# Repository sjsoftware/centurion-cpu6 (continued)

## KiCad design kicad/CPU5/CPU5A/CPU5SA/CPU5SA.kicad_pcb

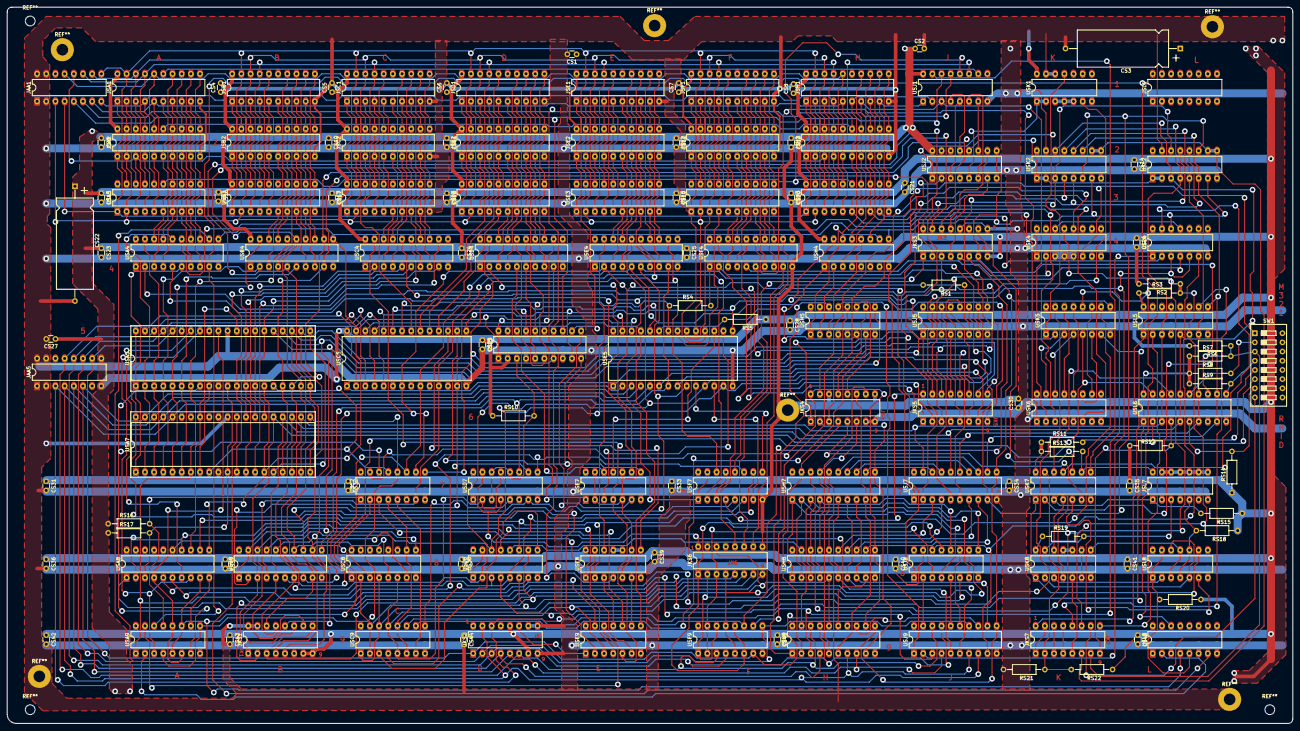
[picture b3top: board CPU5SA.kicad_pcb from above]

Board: 2 copper layers, 355.6 x 198.1 mm, 149 parts (0 on the bottom side), 305 nets.

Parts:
CS1, CS2, CS4, CS5, CS6, CS7, CS8, CS9, CS10, CS11, CS12, CS13, CS14, CS15, CS16, CS17, CS18, CS19, CS20, CS21, CS23, CS24, CS25, CS26, CS27, CS28, CS29, CS30, CS31, CS32, CS33, CS34, CS35, CS36, CS37, CS38, CS39, CS40, CS41, CS42, CS43, CS44, CS45, CS46: 100nF; C_Disc_D3.0mm_W1.6mm_P2.54mm
CS3, CS22: 150uF; CP_Axial_L25.0mm_D10.0mm_P31.75mm_Horizontal
JAA1, JAA5: Conn_02x08_Counter_Clockwise; DIP-16_W7.62mm_cent_socket
JKS1, JKS2, JKS3, JKS4, JKS5, JKS6, JKS7: Conn_02x08_Counter_Clockwise; DIP-16_W7.62mm_cent_socket_ud
JSA1: Conn_02x10_Counter_Clockwise; DIP-20_W7.62mm_cent_socket
JSA2: Conn_02x10_Counter_Clockwise; DIP-20_W7.62mm_cent_padsonly
JSB1: Conn_02x10_Counter_Clockwise; DIP-20_W7.62mm_cent_socket
JSB2: Conn_02x10_Counter_Clockwise; DIP-20_W7.62mm_cent_padsonly
JSC1: Conn_02x10_Counter_Clockwise; DIP-20_W7.62mm_cent_socket
JSC2: Conn_02x10_Counter_Clockwise; DIP-20_W7.62mm_cent_padsonly
JSD1: Conn_02x10_Counter_Clockwise; DIP-20_W7.62mm_cent_socket
JSD2: Conn_02x10_Counter_Clockwise; DIP-20_W7.62mm_cent_padsonly
JSE1: Conn_02x10_Counter_Clockwise; DIP-20_W7.62mm_cent_socket
JSE2: Conn_02x10_Counter_Clockwise; DIP-20_W7.62mm_cent_padsonly
JSF1: Conn_02x10_Counter_Clockwise; DIP-20_W7.62mm_cent_socket
JSF2: Conn_02x10_Counter_Clockwise; DIP-20_W7.62mm_cent_padsonly
JSH1: Conn_02x10_Counter_Clockwise; DIP-20_W7.62mm_cent_socket
JSH2: Conn_02x10_Counter_Clockwise; DIP-20_W7.62mm_cent_padsonly
JSL1: Conn_02x08_Counter_Clockwise; DIP-16_W7.62mm_cent_padsonly
JSL7: Conn_02x07_Counter_Clockwise; DIP-14_W7.62mm_cent_socket
RS1: 47R; R_Axial_DIN0207_L6.3mm_D2.5mm_P11.43mm_Horizontal
RS2, RS21: 330R; R_Axial_DIN0207_L6.3mm_D2.5mm_P11.43mm_Horizontal
RS3, RS7, RS22: 220R; R_Axial_DIN0207_L6.3mm_D2.5mm_P11.43mm_Horizontal
RS4: 100R; R_Axial_DIN0207_L6.3mm_D2.5mm_P11.43mm_Horizontal
RS5, RS10, RS13, RS15, RS16, RS18, RS19, RS20: 1k; R_Axial_DIN0207_L6.3mm_D2.5mm_P11.43mm_Horizontal
RS6: 330; R_Axial_DIN0207_L6.3mm_D2.5mm_P11.43mm_Horizontal
RS8, RS9, RS11, RS12, RS14: 4k7; R_Axial_DIN0207_L6.3mm_D2.5mm_P11.43mm_Horizontal
RS17: 470R; R_Axial_DIN0207_L6.3mm_D2.5mm_P11.43mm_Horizontal
SW1: SW_DIP_x08; SW_DIP_SPSTx08_Slide_9.78x22.5mm_W7.62mm_P2.54mm
USA3: 6349; DIP-20_W7.62mm_cent_socketchip
USA4, USA8: 74LS377; DIP-20_W7.62mm_cent
USA5, USA7: AM2901; DIP-40_W15.24mm_cent_socketchip
USA9: 74LS253; DIP-16_W7.62mm_cent
USB3: 6349; DIP-20_W7.62mm_cent_socketchip
USB4: 74LS377; DIP-20_W7.62mm_cent
USB8: 74LS240; DIP-20_W7.62mm_cent
USC3: 6349; DIP-20_W7.62mm_cent_socketchip
USC4: 74LS377; DIP-20_W7.62mm_cent
USC5: AM2909; DIP-28_W15.24mm_cent_socketchip
USC7: 74LS151; DIP-16_W7.62mm_cent
USC8: 74LS368; DIP-16_W7.62mm_cent
USC9: 74LS298; DIP-16_W7.62mm_cent
USD3: 6349; DIP-20_W7.62mm_cent_socketchip
USD4: 74LS377; DIP-20_W7.62mm_cent
USD5: AM2911; DIP-20_W7.62mm_cent_socketchip
USD7: 74LS151; DIP-16_W7.62mm_cent
USD8: 74LS153; DIP-16_W7.62mm_cent
USE3: 6349; DIP-20_W7.62mm_cent_socketchip
USE4: 74LS377; DIP-20_W7.62mm_cent
USE5: AM2909; DIP-28_W15.24mm_cent_socketchip
USE7, USE8: 74LS00; DIP-14_W7.62mm_cent
USE9: 74LS04; DIP-14_W7.62mm_cent
USF3: 6349; DIP-20_W7.62mm_cent_socketchip
USF4: 74LS377; DIP-20_W7.62mm_cent
USF7: 74LS153; DIP-16_W7.62mm_cent
USF9: 74LS298; DIP-16_W7.62mm_cent
USH3: 6349; DIP-20_W7.62mm_cent_socketchip
USH4: 74LS174; DIP-16_W7.62mm_cent
USH5: 74LS138; DIP-16_W7.62mm_cent
USH7, USH8: 74LS208; DIP-20_W7.62mm_cent_socket
USH9: 74LS377; DIP-20_W7.62mm_cent
USJ1: 74LS139; DIP-16_W7.62mm_cent
USJ2: 74LS174; DIP-16_W7.62mm_cent
USJ5: 74LS151; DIP-16_W7.62mm_cent
USJ7: 74LS374; DIP-20_W7.62mm_cent
USJ8: 74LS157; DIP-16_W7.62mm_cent
USJ9: 74LS377; DIP-20_W7.62mm_cent
USK1: 7437; DIP-14_W7.62mm_cent
USK2: 74LS173; DIP-16_W7.62mm_cent
USK4, USK6: 74LS138; DIP-16_W7.62mm_cent
USK5: 74LS174; DIP-16_W7.62mm_cent
USK7: 74LS04; DIP-14_W7.62mm_cent
USK8: 74LS00; DIP-14_W7.62mm_cent
USL2: 74LS173; DIP-16_W7.62mm_cent
USL4: 74LS02; DIP-14_W7.62mm_cent
USL5: 74LS368; DIP-16_W7.62mm_cent
USL6: 74LS240; DIP-20_W7.62mm_cent
USL8: 74LS74; DIP-14_W7.62mm_cent
USL9: 74LS153; DIP-16_W7.62mm_cent

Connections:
15MHz: JKS7.5, USK8.5
ALU.A0: USA5.4 (A0), USA7.4 (A0), USB4.2 (Q0)
ALU.A1: USA4.19 (Q7), USA5.3 (A1), USA7.3 (A1)
ALU.A2: USA4.16 (Q6), USA5.2 (A2), USA7.2 (A2)
ALU.A3: USA4.6 (Q2), USA5.1 (A3), USA7.1 (A3)
ALU.B0: JKS3.2, USA5.17 (B0), USA7.17 (B0), USB4.9 (Q3)
ALU.B1: JKS3.14, USA5.18 (B1), USA7.18 (B1), USB4.12 (Q4)
ALU.B2: JKS3.15, USA5.19 (B2), USA7.19 (B2), USB4.15 (Q5)
ALU.B3: JKS3.16, USA5.20 (B3), USA7.20 (B3), USB4.5 (Q1)
ALU.C: USA5.33 (Cn+4), USA8.8 (D3), USA9.3 (I3a)
ALU.HC: USA5.29 (Cn), USA7.33 (Cn+4), USA8.13 (D4)
ALU.I0: USA5.12 (I0), USA7.12 (I0), USC4.6 (Q2)
ALU.I1: USA5.13 (I1), USA7.13 (I1), USC4.9 (Q3)
ALU.I2: USA5.14 (I2), USA7.14 (I2), USC4.12 (Q4)
ALU.I3: USA5.26 (I3), USA7.26 (I3), USC4.15 (Q5)
ALU.I4: USA5.28 (I4), USA7.28 (I4), USC4.5 (Q1)
ALU.I5: USA5.27 (I5), USA7.27 (I5), USC4.2 (Q0)
ALU.I6: USA5.5 (I6), USA7.5 (I6), USB4.19 (Q7)
ALU.I7: USA5.7 (I7), USA7.7 (I7), USA9.1 (OEa), USB4.16 (Q6), USE9.13
ALU.I8: USA5.6 (I8), USA7.6 (I8), USB4.6 (Q2)
ALU.Q0: USA7.21 (Q0_LO/RI), USA9.4 (I2a), USA9.9 (Zb), USC7.12 (I7)
ALU.RAM0: USA5.16 (Q3_RO/LI), USA7.9 (RAM0_LO/RI), USC7.13 (I6)
ALU.RAM7: USA5.8 (RAM3_RO/LI), USA9.7 (Za), USC7.14 (I5)
ALU.S: USA5.31 (F3), USA8.4 (D1), USA9.6 (I0a), USA9.12 (I2b)
ALU.V: USA5.34 (OVR), USA8.7 (D2)
ALU.Z: RS17.2, USA5.11 (F=0), USA7.11 (F=0), USA8.3 (D0)
ALU/~PROM: JKS2.11, USE9.1
BUSCLK1: JKS4.5, USK7.6
C: USA7.29 (Cn), USL9.7 (Za)
CC.F: JKS6.7, USC8.6 (I3), USC9.5 (I1c), USC9.13 (Qc), USD7.2 (I2), USD7.13 (I6)
CC.L: JKS6.8, USC7.4 (I0), USC8.10 (I4), USC9.6 (I1d), USC9.12 (Qd), USE9.3
CC.M: JKS6.6, USC8.4 (I2), USC9.1 (I1b), USC9.14 (Qb), USD8.6 (I0a)
CC.V: JKS6.5, USC8.2 (I1), USC9.2 (I1a), USC9.15 (Qa), USD8.10 (I0b)
CL0: JKS6.1, USF9.6 (I1d), USF9.12 (Qd), USJ8.13 (I1d)
CL1: JKS6.4, USF9.5 (I1c), USF9.13 (Qc), USJ8.10 (I1c)
CL2: JKS6.2, USF9.1 (I1b), USF9.14 (Qb), USJ8.6 (I1b)
CL3: JKS6.3, USF9.2 (I1a), USF9.15 (Qa), USJ8.3 (I1a)
DIP.1: RS9.2, SW1.4, USL6.11 (I0b)
DIP.2: JKS7.7, RS6.1, RS7.2, SW1.3, USL6.13 (I1b)
DIP.3: RS8.2, SW1.2, USL6.15 (I2b)
DIP.D: JKS7.10, SW1.8
DIP.H: JKS7.8, RS12.2, SW1.6, USL6.4 (I1a)
DIP.I: RS14.2, SW1.7, USL6.6 (I2a)
DIP.M: JKS4.3, SW1.1, USJ2.4 (D1), USK4.6 (E3)
DIP.R: RS11.2, SW1.5, USL6.2 (I0a)
DMA.REQ.Q: JKS5.13, USJ5.14 (I5)
DP0: JKS1.9, USA7.25 (D0), USB8.3 (O3b), USJ7.12 (O4), USK2.11 (D3), USL2.6 (Q3), USL5.9 (O4a), USL6.9 (O0b), USL6.12 (O3a)
DP1: JKS1.10, USA7.24 (D1), USB8.5 (O2b), USJ7.15 (O5), USK2.12 (D2), USL2.5 (Q2), USL5.7 (O3a), USL6.7 (O1b), USL6.14 (O2a)
DP2: JKS1.13, USA7.23 (D2), USB8.7 (O1b), USJ7.16 (O6), USK2.14 (D0), USL2.3 (Q0), USL5.5 (O2a), USL6.5 (O2b), USL6.16 (O1a)
DP3: JKS1.14, USA7.22 (D3), USB8.9 (O0b), USJ7.19 (O7), USK2.13 (D1), USL2.4 (Q1), USL5.3 (O1a), USL6.3 (O3b), USL6.18 (O0a)
DP4: JKS1.11, USA5.25 (D0), USB8.18 (O0a), USC8.9 (O4a), USJ7.9 (O3), USK2.6 (Q3), USL2.11 (D3)
DP5: JKS1.12, USA5.24 (D1), USB8.16 (O1a), USC8.7 (O3a), USJ7.6 (O2), USK2.5 (Q2), USL2.12 (D2)
DP6: JKS1.4, USA5.23 (D2), USB8.14 (O2a), USC8.5 (O2a), USJ7.5 (O1), USK2.3 (Q0), USL2.14 (D0)
DP7: JKS1.5, USA5.22 (D3), USB8.12 (O3a), USC8.3 (O1a), USJ7.2 (O0), USK2.4 (Q1), USL2.13 (D1)
F0: JAA5.3, JKS2.14, USA7.36 (Y0), USE5.5 (R0), USH9.3 (D0), USJ9.3 (D0)
F1: JAA5.4, JKS2.15, USA7.37 (Y1), USE5.4 (R1), USH9.4 (D1), USJ9.8 (D3)
F2: JAA5.5, JKS2.4, USA7.38 (Y2), USE5.3 (R2), USH9.7 (D2), USJ9.7 (D2)
F3: JAA5.6, JKS2.5, USA7.39 (Y3), USE5.2 (R3), USH9.8 (D3), USJ9.4 (D1)
F4: JAA5.10, JKS2.1, USA5.36 (Y0), USC5.5 (R0), USF9.7 (I0d), USH9.13 (D4), USJ9.13 (D4)
F5: JAA5.11, JKS2.2, USA5.37 (Y1), USC5.4 (R1), USF9.9 (I0c), USH9.14 (D5), USJ9.14 (D5)
F6: JAA5.12, JKS2.3, USA5.38 (Y2), USC5.3 (R2), USF9.4 (I0b), USH9.17 (D6), USJ9.17 (D6)
F7: JAA5.13, JKS2.6, USA5.39 (Y3), USC5.2 (R3), USF9.3 (I0a), USH9.18 (D7), USJ9.18 (D7)
FLR.16Z: USD8.13 (I3b), USE9.10
FLR.C: USA8.9 (Q3), USA9.5 (I1a), USA9.11 (I1b), USC7.2 (I2), USL9.4 (I2a)
FLR.HC: USA8.12 (Q4), USF7.5 (I1a)
FLR.S: USA8.5 (Q1), USD8.3 (I3a), USD8.5 (I1a), USF7.6 (I0a)
FLR.V: USA8.6 (Q2), USD7.9 (S2), USF7.11 (I1b)
FLR.Z: USA8.2 (Q0), USA8.14 (D5), USD8.11 (I1b), USE8.2, USF7.10 (I0b)
FP.DELAY: JKS7.11, RS2.1, RS3.2, USL5.6 (I3)
GND: CS1.2, CS2.2, CS3.2, CS4.2, CS5.2, CS6.2, CS7.2, CS8.2, CS9.2, CS10.2, CS11.2, CS12.2, CS13.2, CS14.2, CS15.2, CS16.2, CS17.2, CS18.2, CS19.2, CS20.2, CS21.2, CS22.2, CS23.2, CS24.2, CS25.2, CS26.2, CS27.2, CS28.2, CS29.2, CS30.2, CS31.2, CS32.2, CS33.2, CS34.2, CS35.2, CS36.2, CS37.2, CS38.2, CS39.2, CS40.2, CS41.2, CS42.2, CS43.2, CS44.2, CS45.2, CS46.2, JAA1.1, JAA1.2, JAA1.15, JAA1.16, JAA5.1, JAA5.2, JAA5.15, JAA5.16, JKS1.15, JKS1.16, JKS2.8, JKS2.9, JKS2.10, JKS3.9, JKS3.12, JKS4.9, JKS4.14, JKS6.9, JKS7.3, JKS7.4, JKS7.13, JKS7.14, JSA1.10, JSA2.10, JSB1.10, JSB2.10, JSC1.10, JSC2.10, JSD1.10, JSD2.10, JSE1.10, JSE2.10, JSF1.10, JSF2.10, JSH1.10, JSH2.10, JSL7.2, JSL7.4, JSL7.6, JSL7.7, RS2.2, RS4.2, RS6.2, RS21.2, SW1.9, SW1.10, SW1.11, SW1.12, SW1.13, SW1.14, SW1.15, SW1.16, USA3.10 (GND), USA4.1 (~E), USA4.10 (GND), USA5.30 (GND), USA7.30 (GND), USA8.10 (GND), USA9.8 (GND), USA9.10 (I0b), USB3.10 (GND), USB4.1 (~E), USB4.10 (GND), USB8.10 (GND), USC3.10 (GND), USC4.1 (~E), USC4.10 (GND), USC5.6 (OR3), USC5.8 (OR2), USC5.10 (OR1), USC5.12 (OR0), USC5.14 (GND), USC7.8 (GND), USC8.8 (GND), USC9.8 (GND), USD3.10 (GND), USD4.1 (~E), USD4.10 (GND), USD5.4 (D3), USD5.8 (GND), USD7.1 (I3), USD7.8 (GND), USD8.1 (Ea), USD8.8 (GND), USD8.15 (Eb), USE3.10 (GND), USE4.1 (~E), USE4.10 (GND), USE5.14 (GND), USE7.7 (GND), USE8.7 (GND), USE9.7 (GND), USF3.10 (GND), USF4.1 (~E), USF4.10 (GND), USF7.3 (I3a), USF7.8 (GND), USF7.13 (I3b), USF9.8 (GND), USH3.10 (GND), USH4.8 (GND), USH5.4 (E1), USH5.5 (E2), USH5.8 (GND), USH7.10 (GND), USH7.16 (~OE), USH8.10 (GND), USH8.16 (~OE), USH9.10 (GND), USJ1.8 (GND), USJ2.8 (GND), USJ5.8 (GND), USJ7.10 (GND), USJ8.8 (GND), USJ8.15 (E), USJ9.10 (GND), USK1.7 (GND), USK1.12, USK1.13, USK2.8 (GND), USK2.15 (Mr), USK4.3 (A2), USK4.4 (E1), USK4.5 (E2), USK4.8 (GND), USK5.8 (GND), USK6.4 (E1), USK6.5 (E2), USK6.8 (GND), USK7.7 (GND), USK8.7 (GND), USL2.8 (GND), USL2.15 (Mr), USL4.7 (GND), USL5.4 (I2), USL5.8 (GND), USL6.8 (I3a), USL6.10 (GND), USL8.7 (GND), USL9.1 (Ea), USL9.3 (I3a), USL9.6 (I0a), USL9.8 (GND)
INT: JKS5.12, USJ5.12 (I7)
JSR?: RS1.2, USE7.2, USE7.5, USE7.10, USE7.13, USE8.5, USE8.9
MC0: JSH1.6, JSH2.6, USH3.6 (D0), USJ1.2 (A0), USK6.1 (A0)
MC1: JSH1.7, JSH2.7, USH3.7 (D1), USJ1.3 (A1), USK6.2 (A1)
MC2: JSH1.8, JSH2.8, USH3.8 (D2), USK6.3 (A2)
MC3: JSH1.9, JSH2.9, USH3.9 (D3), USJ1.1 (E), USK6.6 (E3)
MC4: JSH1.11, JSH2.11, USH3.11 (D4), USH4.11 (D3)
MC5: JSH1.12, JSH2.12, USH3.12 (D5), USH4.3 (D0)
MC6: JSH1.13, JSH2.13, USH3.13 (D6), USH4.13 (D4)
MC7: JSH1.14, JSH2.14, USH3.14 (D7), USH4.14 (D5)
MC8: JSF1.6, JSF2.6, USF3.6 (D0), USF4.18 (D7)
MC9: JSF1.7, JSF2.7, USF3.7 (D1), USF4.17 (D6)
MC10: JSF1.8, JSF2.8, USF3.8 (D2), USF4.7 (D2)
MC11: JSF1.9, JSF2.9, USF3.9 (D3), USF4.8 (D3)
MC12: JSF1.11, JSF2.11, USF3.11 (D4), USF4.13 (D4)
MC13: JSF1.12, JSF2.12, USF3.12 (D5), USF4.14 (D5)
MC14: JSF1.13, JSF2.13, USF3.13 (D6), USF4.4 (D1)
MC15: JSF1.14, JSF2.14, USF3.14 (D7), USF4.3 (D0)
MC16: JSE1.6, JSE2.6, USE3.6 (D0), USE4.18 (D7)
MC17: JSE1.7, JSE2.7, USE3.7 (D1), USE4.17 (D6)
MC18: JSE1.8, JSE2.8, USE3.8 (D2), USE4.7 (D2)
MC19: JSE1.9, JSE2.9, USE3.9 (D3), USE4.8 (D3)
MC20: JSE1.11, JSE2.11, USE3.11 (D4), USE4.13 (D4)
MC21: JSE1.12, JSE2.12, USE3.12 (D5), USE4.14 (D5)
MC22: JSE1.13, JSE2.13, USE3.13 (D6), USE4.4 (D1)
MC23: JSE1.14, JSE2.14, USE3.14 (D7), USE4.3 (D0)
MC24: JSD1.6, JSD2.6, USD3.6 (D0), USD4.18 (D7)
MC25: JSD1.7, JSD2.7, USD3.7 (D1), USD4.17 (D6)
MC26: JSD1.8, JSD2.8, USD3.8 (D2), USD4.7 (D2)
MC27: JSD1.9, JSD2.9, USD3.9 (D3), USD4.8 (D3)
MC28: JSD1.11, JSD2.11, USD3.11 (D4), USD4.13 (D4)
MC29: JSD1.12, JSD2.12, USD3.12 (D5), USD4.14 (D5)
MC30: JSD1.13, JSD2.13, USD3.13 (D6), USD4.4 (D1)
MC31: JSD1.14, JSD2.14, USD3.14 (D7), USD4.3 (D0)
MC32: JSC1.6, JSC2.6, USC3.6 (D0), USC4.18 (D7)
MC33: JSC1.7, JSC2.7, USC3.7 (D1), USC4.17 (D6)
MC34: JSC1.8, JSC2.8, USC3.8 (D2), USC4.7 (D2)
MC35: JSC1.9, JSC2.9, USC3.9 (D3), USC4.8 (D3)
MC36: JSC1.11, JSC2.11, USC3.11 (D4), USC4.13 (D4)
MC37: JSC1.12, JSC2.12, USC3.12 (D5), USC4.14 (D5)
MC38: JSC1.13, JSC2.13, USC3.13 (D6), USC4.4 (D1)
MC39: JSC1.14, JSC2.14, USC3.14 (D7), USC4.3 (D0)
MC40: JSB1.6, JSB2.6, USB3.6 (D0), USB4.18 (D7)
MC41: JSB1.7, JSB2.7, USB3.7 (D1), USB4.17 (D6)
MC42: JSB1.8, JSB2.8, USB3.8 (D2), USB4.7 (D2)
MC43: JSB1.9, JSB2.9, USB3.9 (D3), USB4.8 (D3)
MC44: JSB1.11, JSB2.11, USB3.11 (D4), USB4.13 (D4)
MC45: JSB1.12, JSB2.12, USB3.12 (D5), USB4.14 (D5)
MC46: JSB1.13, JSB2.13, USB3.13 (D6), USB4.4 (D1)
MC47: JSB1.14, JSB2.14, USB3.14 (D7), USB4.3 (D0)
MC48: JSA1.6, JSA2.6, USA3.6 (D0), USA4.18 (D7)
MC49: JSA1.7, JSA2.7, USA3.7 (D1), USA4.17 (D6)
MC50: JSA1.8, JSA2.8, USA3.8 (D2), USA4.7 (D2)
MC51: JSA1.9, JSA2.9, USA3.9 (D3), USA4.8 (D3)
MC52: JSA1.11, JSA2.11, USA3.11 (D4), USA4.13 (D4)
MC53: JSA1.12, JSA2.12, USA3.12 (D5), USA4.14 (D5)
MC54: JSA1.13, JSA2.13, USA3.13 (D6), USA4.4 (D1)
MC55: JSA1.14, JSA2.14, USA3.14 (D7), USA4.3 (D0)
MCA0: JAA1.4, JSA1.1, JSA2.1, JSB1.1, JSB2.1, JSC1.1, JSC2.1, JSD1.1, JSD2.1, JSE1.1, JSE2.1, JSF1.1, JSF2.1, JSH1.1, JSH2.1, USA3.1 (A0), USB3.1 (A0), USC3.1 (A0), USD3.1 (A0), USE3.1 (A0), USE5.18 (Y0), USF3.1 (A0), USH3.1 (A0)
MCA1: JAA1.3, JSA1.2, JSA2.2, JSB1.2, JSB2.2, JSC1.2, JSC2.2, JSD1.2, JSD2.2, JSE1.2, JSE2.2, JSF1.2, JSF2.2, JSH1.2, JSH2.2, USA3.2 (A1), USB3.2 (A1), USC3.2 (A1), USD3.2 (A1), USE3.2 (A1), USE5.19 (Y1), USF3.2 (A1), USH3.2 (A1)
MCA2: JAA1.12, JSA1.3, JSA2.3, JSB1.3, JSB2.3, JSC1.3, JSC2.3, JSD1.3, JSD2.3, JSE1.3, JSE2.3, JSF1.3, JSF2.3, JSH1.3, JSH2.3, USA3.3 (A2), USB3.3 (A2), USC3.3 (A2), USD3.3 (A2), USE3.3 (A2), USE5.20 (Y2), USF3.3 (A2), USH3.3 (A2)
MCA3: JAA1.8, JSA1.4, JSA2.4, JSB1.4, JSB2.4, JSC1.4, JSC2.4, JSD1.4, JSD2.4, JSE1.4, JSE2.4, JSF1.4, JSF2.4, JSH1.4, JSH2.4, USA3.4 (A3), USB3.4 (A3), USC3.4 (A3), USD3.4 (A3), USE3.4 (A3), USE5.21 (Y3), USF3.4 (A3), USH3.4 (A3)
MCA4: JAA1.7, JSA1.5, JSA2.5, JSB1.5, JSB2.5, JSC1.5, JSC2.5, JSD1.5, JSD2.5, JSE1.5, JSE2.5, JSF1.5, JSF2.5, JSH1.5, JSH2.5, USA3.5 (A4), USB3.5 (A4), USC3.5 (A4), USC5.18 (Y0), USD3.5 (A4), USE3.5 (A4), USF3.5 (A4), USH3.5 (A4)
MCA5: JAA1.13, JSA1.16, JSA2.16, JSB1.16, JSB2.16, JSC1.16, JSC2.16, JSD1.16, JSD2.16, JSE1.16, JSE2.16, JSF1.16, JSF2.16, JSH1.16, JSH2.16, USA3.16 (A5), USB3.16 (A5), USC3.16 (A5), USC5.19 (Y1), USD3.16 (A5), USE3.16 (A5), USF3.16 (A5), USH3.16 (A5)
MCA6: JAA1.11, JSA1.17, JSA2.17, JSB1.17, JSB2.17, JSC1.17, JSC2.17, JSD1.17, JSD2.17, JSE1.17, JSE2.17, JSF1.17, JSF2.17, JSH1.17, JSH2.17, USA3.17 (A6), USB3.17 (A6), USC3.17 (A6), USC5.20 (Y2), USD3.17 (A6), USE3.17 (A6), USF3.17 (A6), USH3.17 (A6)
MCA7: JAA1.10, JSA1.18, JSA2.18, JSB1.18, JSB2.18, JSC1.18, JSC2.18, JSD1.18, JSD2.18, JSE1.18, JSE2.18, JSF1.18, JSF2.18, JSH1.18, JSH2.18, USA3.18 (A7), USB3.18 (A7), USC3.18 (A7), USC5.21 (Y3), USD3.18 (A7), USE3.18 (A7), USF3.18 (A7), USH3.18 (A7)
MCA8: JAA1.9, JSA1.19, JSA2.19, JSB1.19, JSB2.19, JSC1.19, JSC2.19, JSD1.19, JSD2.19, JSE1.19, JSE2.19, JSF1.19, JSF2.19, JSH1.19, JSH2.19, USA3.19 (A8), USB3.19 (A8), USC3.19 (A8), USD3.19 (A8), USD5.12 (Y0), USE3.19 (A8), USF3.19 (A8), USH3.19 (A8)
MCA9: JAA1.5, USD5.13 (Y1), USJ1.14 (A0)
MCA10: JAA1.6, USD5.14 (Y2), USJ1.13 (A1)
MCS0: USA3.15 (~E), USB3.15 (~E), USC3.15 (~E), USD3.15 (~E), USE3.15 (~E), USF3.15 (~E), USH3.15 (~E), USJ1.12 (O0)
MCS1: JSA2.15, JSB2.15, JSC2.15, JSD2.15, JSE2.15, JSF2.15, JSH2.15, USJ1.11 (O1)
MCS2: JSA1.15, JSB1.15, JSC1.15, JSD1.15, JSE1.15, JSF1.15, JSH1.15, USJ1.10 (O2)
MUX.F: USC9.9 (I0c), USD7.5 (Z)
MUX.L: USC7.5 (Z), USC9.7 (I0d)
MUX.M: USC9.4 (I0b), USD8.7 (Za)
MUX.V: USC9.3 (I0a), USD8.9 (Zb)
NOT.MEM: JKS5.15, USJ5.1 (I3)
unnamed: JSL7.8, JSL7.9, JSL7.10, JSL7.11, JSL7.12, JSL7.13
unnamed: RS1.1, USJ5.6 (~Z)
unnamed: RS4.1, USC5.22 (~OE), USD5.16 (~OE), USE5.22 (~OE)
unnamed: USA5.9 (RAM0_LO/RI), USA7.8 (RAM3_RO/LI)
unnamed: USA5.21 (Q0_LO/RI), USA7.16 (Q3_RO/LI)
unnamed: USA5.40 (~OE), USA7.40 (~OE), USE9.2
unnamed: USA8.15 (Q5), USE8.1
unnamed: USA9.15 (OEb), USE9.12
unnamed: USC5.23 (Cn), USE5.24 (Cn+4)
unnamed: USC5.24 (Cn+4), USD5.17 (Cn)
unnamed: USC7.3 (I1), USE9.4
unnamed: USE8.3, USE9.11
unnamed: USE8.6, USE9.9
unnamed: USE8.10, USE8.11
unnamed: USE8.13, USE9.6
unnamed: USJ1.4 (O0), USJ2.13 (D4)
unnamed: USJ1.5 (O1), USJ2.3 (D0)
unnamed: USJ1.6 (O2), USJ2.6 (D2)
unnamed: USJ1.7 (O3), USJ2.11 (D3)
unnamed: USJ1.15 (E), USK7.8
unnamed: USJ2.1 (~Mr), USK1.11, USK5.1 (~Mr)
unnamed: USJ5.3 (I1), USL4.4
unnamed: USJ8.2 (I0a), USJ9.19 (Q7)
unnamed: USJ8.5 (I0b), USJ9.16 (Q6)
unnamed: USJ8.11 (I0c), USJ9.15 (Q5)
unnamed: USK1.3, USK1.4, USK1.5
unnamed: USK5.3 (D0), USK6.15 (O0)
unnamed: USK5.4 (D1), USK6.14 (O1)
unnamed: USK5.6 (D2), USK6.11 (O4)
unnamed: USK5.11 (D3), USK6.10 (O5)
unnamed: USK5.13 (D4), USK6.12 (O3)
unnamed: USK5.14 (D5), USK6.13 (O2)
unnamed: USK7.1, USK8.1, USL8.9 (Q)
unnamed: USK7.4, USK8.12
unnamed: USK7.5, USL8.6 (~Q)
unnamed: USK7.11, USL4.13
unnamed: USK7.12, USL6.17 (I3b)
unnamed: USK8.2, USL8.5 (Q), USL8.12 (D)
unnamed: USK8.3, USL8.2 (D)
unnamed: USK8.6, USK8.9
unnamed: USK8.8, USL8.3 (C), USL8.11 (C)
unnamed: USK8.10, USK8.11
OR0: USE5.12 (OR0), USF7.7 (Za)
OR1: USE5.10 (OR1), USF7.9 (Zb)
OR2: JKS5.7, USE5.8 (OR2)
OR3: JKS5.11, USE5.6 (OR3)
PE: JKS5.6, USJ5.13 (I6)
PHI1: JKS3.5, USK7.2
PHI2: JKS3.7, USA4.11 (CP), USA5.15 (CP), USA7.15 (CP), USA8.11 (CP), USB4.11 (CP), USC4.11 (CP), USC5.27 (CP), USD4.11 (CP), USD5.1 (CP), USE4.11 (CP), USE5.27 (CP), USF4.11 (CP), USH4.9 (Cp), USH9.11 (CP), USJ2.9 (Cp), USJ7.11 (Cp), USJ9.11 (CP), USK2.7 (Cp), USK5.9 (Cp), USL2.7 (Cp), USL4.12
PL4: USH4.10 (Q3), USH5.1 (A0)
PL5: USH4.2 (Q0), USH5.2 (A1)
PL6: USH4.12 (Q4), USH5.3 (A2)
PL7: JKS5.3, USH4.15 (Q5)
PL8: JKS5.2, USF4.19 (Q7)
PL9: JKS5.1, USF4.16 (Q6)
PL10: JKS6.12, USF4.6 (Q2)
PL11: JKS6.11, USF4.9 (Q3)
PL12: JKS6.10, USF4.12 (Q4)
PL13: USF4.15 (Q5), USK4.1 (A0)
PL14: USF4.5 (Q1), USK4.2 (A1)
PL15: USF4.2 (Q0), USJ5.7 (~E)
PL16: USB8.17 (I3b), USD8.14 (S0), USE4.19 (Q7), USE5.13 (D0), USJ5.11 (S0)
PL17: USB8.15 (I2b), USD8.2 (S1), USE4.16 (Q6), USE5.11 (D1), USJ5.10 (S1)
PL18: USB8.13 (I1b), USD7.7 (~E), USE4.6 (Q2), USE5.9 (D2), USJ5.9 (S2)
PL19: USB8.11 (I0b), USD7.11 (S0), USE4.9 (Q3), USE5.7 (D3)
PL20: USB8.2 (I0a), USC5.13 (D0), USD7.10 (S1), USE4.12 (Q4), USF7.14 (S0)
PL21: USB8.4 (I1a), USC5.11 (D1), USC7.7 (~E), USE4.15 (Q5), USF7.2 (S1)
PL22: JKS5.8, USB8.6 (I2a), USC5.9 (D2), USC7.11 (S0), USE4.5 (Q1)
PL23: JKS5.10, USB8.8 (I3a), USC5.7 (D3), USC7.10 (S1), USE4.2 (Q0)
PL24: USC7.9 (S2), USD4.19 (Q7), USD5.7 (D0)
PL25: USD4.16 (Q6), USD5.6 (D1)
PL26: USD4.6 (Q2), USD5.5 (D2)
PL27: USD4.9 (Q3), USE8.4
PL28: USC5.26 (PUP), USD4.12 (Q4), USD5.20 (PUP), USE5.26 (PUP)
PL29: USD4.15 (Q5), USE7.1
PL30: USD4.5 (Q1), USE7.12
PL31: USD4.2 (Q0), USE7.9
PL32: USC4.19 (Q7), USE7.4, USE9.5
PL33: JKS5.9, USC4.16 (Q6), USF7.1 (Ea), USF7.15 (Eb)
PL51: USA4.9 (Q3), USA9.14 (A0), USL9.14 (S0)
PL52: USA4.12 (Q4), USA9.2 (A1), USL9.2 (S1)
PL53: USA4.15 (Q5), USL4.2
PL54: USA4.5 (Q1), USE8.12
PL55: USA4.2 (Q0), USJ8.1 (S)
PUS5: RS5.2, USE5.23 (Cn), USH4.1 (~Mr), USH5.6 (E3)
PUS10: RS10.2, USD5.3 (~RE), USD7.3 (I1), USD7.12 (I7), USD7.14 (I5)
PUS16: RS16.2, USA9.13 (I3b), USC7.1 (I3)
PUS20: RS20.2, USL8.1 (~R), USL8.13 (~R), USL9.5 (I1a)
R0: JKS4.4, USH7.19 (D3), USH9.2 (Q0)
R1: JKS4.10, USH7.5 (D2), USH9.5 (Q1)
R2: JKS4.11, USH7.9 (D1), USH9.6 (Q2)
R3: JKS4.2, USH7.11 (D0), USH9.9 (Q3)
R4: JKS4.16, USC7.15 (I4), USH8.11 (D0), USH9.12 (Q4)
R5: JKS6.16, USD7.4 (I0), USD7.15 (I4), USH8.9 (D1), USH9.15 (Q5)
R6: JKS6.14, USD8.4 (I2a), USH8.5 (D2), USH9.16 (Q6)
R7: JKS6.15, USD8.12 (I2b), USH8.19 (D3), USH9.19 (Q7)
RDONLY: JKS7.12, USL5.10 (I4)
REG.RDONLY: JKS5.14, USJ5.15 (I4)
RF.0: USH7.15 (Q3), USJ7.13 (D4)
RF.1: USH7.14 (Q2), USJ7.14 (D5)
RF.2: USH7.13 (Q1), USJ7.17 (D6)
RF.3: USH7.12 (Q0), USJ7.18 (D7)
RF.4: USH8.12 (Q0), USJ7.8 (D3)
RF.5: USH8.13 (Q1), USJ7.7 (D2)
RF.6: USH8.14 (Q2), USJ7.4 (D1)
RF.7: USH8.15 (Q3), USJ7.3 (D0)
RI.0: USH7.18 (A7), USH8.18 (A7), USL4.1
RI.4: USH7.4 (A3), USH8.4 (A3), USJ8.12 (Zd)
RI.5: USH7.3 (A2), USH8.3 (A2), USJ8.9 (Zc)
RI.6: USH7.2 (A1), USH8.2 (A1), USJ8.7 (Zb)
RI.7: USH7.1 (A0), USH8.1 (A0), USJ8.4 (Za)
RIR.0: USJ5.2 (I2), USJ9.2 (Q0), USL4.3, USL4.5
RIR.1: USH7.8 (A6), USH8.8 (A6), USJ9.9 (Q3)
RIR.2: USH7.7 (A5), USH8.7 (A5), USJ9.6 (Q2)
RIR.3: USH7.6 (A4), USH8.6 (A4), USJ9.5 (Q1)
RIR.4: USJ8.14 (I0d), USJ9.12 (Q4), USL4.6
R/F: JKS7.2, RS21.1, RS22.2, USK7.13
S00: USE5.16 (S0), USE7.3
S01: USE5.17 (S1), USE7.11
S10: USC5.16 (S0), USD5.10 (S0), USE7.8
S11: USC5.17 (S1), USE8.8
S21: USD5.11 (S1), USE7.6
SL7.1: JSL7.1, RS15.2, USK7.3, USK8.4
SL7.3: JSL7.3, RS19.2, USK8.13
SL7.5: JSL7.5, RS18.2, USL8.4 (~S), USL8.10 (~S)
SL7.14: JSL7.14, RS13.2, USK7.9
VCC: CS2.1, CS3.1, CS4.1, CS5.1, CS6.1, CS7.1, CS8.1, CS9.1, CS10.1, CS11.1, CS12.1, CS13.1, CS14.1, CS15.1, CS16.1, CS17.1, CS18.1, CS19.1, CS20.1, CS21.1, CS22.1, CS23.1, CS24.1, CS25.1, CS26.1, CS27.1, CS28.1, CS29.1, CS30.1, CS31.1, CS32.1, CS33.1, CS34.1, CS35.1, CS36.1, CS37.1, CS38.1, CS39.1, CS40.1, CS41.1, CS42.1, CS43.1, CS44.1, CS45.1, CS46.1, JAA5.8, JAA5.9, JKS1.7, JKS1.8, JKS2.7, JKS2.12, JKS3.8, JKS4.7, JKS4.8, JKS7.1, JKS7.15, JSA1.20, JSA2.20, JSB1.20, JSB2.20, JSC1.20, JSC2.20, JSD1.20, JSD2.20, JSE1.20, JSE2.20, JSF1.20, JSF2.20, JSH1.20, JSH2.20, RS3.1, RS5.1, RS7.1, RS8.1, RS9.1, RS10.1, RS11.1, RS12.1, RS13.1, RS14.1, RS15.1, RS16.1, RS17.1, RS18.1, RS19.1, RS20.1, RS22.1, USA3.20 (VCC), USA4.20 (VCC), USA5.10 (VCC), USA7.10 (VCC), USA8.20 (VCC), USA9.16 (VCC), USB3.20 (VCC), USB4.20 (VCC), USB8.20 (VCC), USC3.20 (VCC), USC4.20 (VCC), USC5.28 (VCC), USC7.16 (VCC), USC8.16 (VCC), USC9.16 (VCC), USD3.20 (VCC), USD4.20 (VCC), USD5.2 (VCC), USD7.16 (VCC), USD8.16 (VCC), USE3.20 (VCC), USE4.20 (VCC), USE5.28 (VCC), USE7.14 (VCC), USE8.14 (VCC), USE9.14 (VCC), USF3.20 (VCC), USF4.20 (VCC), USF7.16 (VCC), USF9.16 (VCC), USH3.20 (VCC), USH4.16 (VCC), USH5.16 (VCC), USH7.20 (VCC), USH8.20 (VCC), USH9.20 (VCC), USJ1.16 (VCC), USJ2.16 (VCC), USJ5.16 (VCC), USJ7.20 (VCC), USJ8.16 (VCC), USJ9.20 (VCC), USK1.14 (VCC), USK2.16 (VCC), USK4.16 (VCC), USK5.16 (VCC), USK6.16 (VCC), USK7.14 (VCC), USK8.14 (VCC), USL2.16 (VCC), USL4.14 (VCC), USL5.16 (VCC), USL6.20 (VCC), USL8.14 (VCC), USL9.16 (VCC)
~BAD.PG: JKS3.1, USF7.12 (I2b)
~BUS.ABT: USK4.14 (O1), USL4.11
~BUS.READY: JKS3.10, USK7.10
~BUS.WAIT: JKS4.15, USK4.12 (O3)
~BUSY.Q: JKS5.5, USJ5.4 (I0)
~DMA.INT: JKS7.9, USL5.2 (I1)
~FE: USC5.25 (~FE), USD5.19 (~FE), USE5.25 (~FE), USE9.8
~LOAD.CCR: USC9.10 (S), USH5.7 (O7)
~LOAD.CLR: USF9.10 (S), USH5.12 (O3)
~LOAD.FLR: USA8.1 (~E), USK4.13 (O2)
~LOAD.MAP: JKS4.12, USH5.11 (O4)
~LOAD.MAR: JKS4.13, USH5.10 (O5)
~LOAD.RIR: USH5.13 (O2), USJ9.1 (~E)
~LOAD.RR: USH5.14 (O1), USH9.1 (~E)
~LOAD.SAR: USC5.1 (~RE), USE5.1 (~RE), USH5.9 (O6)
~LOAD.SWP: JKS7.6, USK2.9 (E1), USK2.10 (E2), USL2.9 (E1), USL2.10 (E2)
~PHI3: JKS3.6, USC9.11 (Cp), USF9.11 (Cp)
~RDONLY: JKS5.16, USF7.4 (I2a)
~READ.AHI: JKS3.4, USJ2.7 (Q2)
~READ.ALO: JKS3.13, USJ2.10 (Q3)
~READ.CCR: USC8.1 (OEa), USK5.5 (Q1), USL6.19 (OEb)
~READ.CLR: JKS7.16, USK5.12 (Q4), USL5.1 (OEa)
~READ.CONST: USB8.1 (OEa), USB8.19 (OEb), USK5.10 (Q3)
~READ.DB: JKS1.2, USK5.15 (Q5)
~READ.INR: JKS1.3, USK5.7 (Q2), USL6.1 (OEa)
~READ.PF: JKS4.1, USK5.2 (Q0)
~READ.RF: USJ2.2 (Q0), USJ7.1 (OE)
~READ.SWP: USJ2.12 (Q4), USK2.1 (Oe1), USK2.2 (Oe2), USL2.1 (Oe1), USL2.2 (Oe2)
~RESET1: USJ2.5 (Q1), USK1.1, USK1.2
~RESET2: JKS3.3, USC5.15 (~ZERO), USD5.9 (~ZERO), USE5.15 (~ZERO), USK1.6
~WRITE.RF: JKS4.6, USH7.17 (WE), USH8.17 (WE)

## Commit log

2022-04-05 Create LICENSE
2022-04-17 New PDF
2022-04-17 Add microcode word layout
2022-04-18 Added todo list
2022-04-18 Annotated microcode and CPU chip function
2022-04-26 Update for C9
2022-04-26 Corrected description of 74S151
2022-04-26 Update description of C9/D9 registers
2022-04-28 Updated schematic - edge connector ordering now consistent with other schematics
2022-04-30 Correct description of 74LS174s, added info
2022-04-30 Add kicad
2022-04-30 Update PDF
2022-04-30 Add kicad project
2022-05-11 All chips on schematic
2022-06-13 Add more traces, relabeled microcode pipeline register
2022-06-13 Conditional MUX control
2022-06-20 Schematic corrections
2022-06-25 Pins from today's beeping
2022-06-26 Errors corrected
2022-07-09 Redo schematic
2022-08-01 99.9% traces; functional image
2023-02-17 Resync
2023-11-11 CPU5 schematics
2023-11-11 Corrections from CPU5 reverse engineering
2023-11-11 PDFs
2023-11-11 More detail in CPU5 README
2023-11-11 Tidyup
2023-11-17 CPU5 reorg
2023-12-05 Trace separation adjustment
2023-12-06 Trace tidyup and SRAM breakout
2025-12-30 CPU5 revision
